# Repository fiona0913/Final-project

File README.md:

# Final-project
# Portable Soil Monitor

## Project Overview
The Portable Soil Monitor is a device designed for real-time monitoring of soil moisture. It uses a soil moisture sensor to collect data, analyzes trends with a machine learning algorithm, and predicts the next watering time to help users scientifically manage their plants.

---

## Features
- Real-time monitoring of soil moisture levels.
- Machine learning-based trend analysis to predict dryness for the next 1–2 days.
- Stepper motor-driven needle to display soil moisture status.
- LED indicators to provide watering reminders.
- Touch-sensitive button for manual data refresh.
- Solar-powered with backup lithium battery for continuous operation.

---

## Hardware Design

### 1. Overall Sketch

---

### 2. Sensing Device
- **Sensor**: DFRobot Capacitive Soil Moisture Sensor v2 (SEN0193).
- **Functionality**: Measures soil moisture levels and transmits data wirelessly to the main control chip (ESP32).
- **Power**: Solar panel as the primary power source, with a built-in lithium battery as backup.
- **Diagram**:

---

### 3. Display Device
- **Key Components**:
  - **Stepper Motor**: 28BYJ-48, drives a needle to show the soil moisture level.
  - **LEDs**: WS2812B RGB LEDs to indicate watering reminders.
  - **Touch Button**: TTP223 capacitive touch module for manual refresh.
- **Power**: Powered by a 3.7V lithium battery with optimized power consumption for stepper motors and LEDs.
- **Diagram**: *(Insert detailed sketch of the display device here.)*

---

## Communication and Workflow

### 1. Device Communication Flow

### 2. Functional Diagram

---

## Datasheets
The datasheets for all components used in this project can be found in the `datasheets/` folder. Key components include:
- **Soil Moisture Sensor**: SEN0193.
- **Wireless Communication Module**: ESP32-WROOM-32.
- **Stepper Motor**: 28BYJ-48 with ULN2003 driver.
- **RGB LEDs**: WS2812B.
- **Touch Button**: TTP223.
- **Power Management Module**: TP4056.

---

## How to Run the Project
1. Assemble all hardware components according to the design.
2. Upload the code to the ESP32 microcontroller.
3. Power on the device and let it begin monitoring soil moisture and displaying the results.

---

## Repository Structure

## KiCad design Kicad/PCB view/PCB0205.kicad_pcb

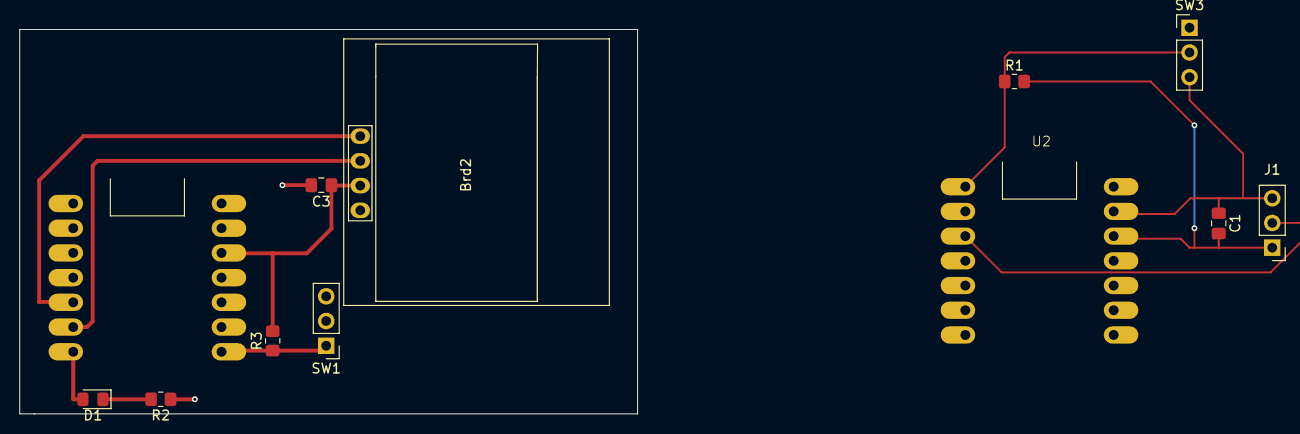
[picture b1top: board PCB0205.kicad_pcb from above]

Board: 2 copper layers, 63.5 x 39.5 mm, 12 parts (0 on the bottom side), 9 nets.

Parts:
Brd2: SSD1306; 128x64OLED
C1, C3: C; C_0805_2012Metric_Pad1.18x1.45mm_HandSolder
D1: LED; LED_0805_2012Metric_Pad1.15x1.40mm_HandSolder
J1: Soil Mositure Sen; PinHeader_1x03_P2.54mm_Vertical
R1, R2, R3: R; R_0805_2012Metric_Pad1.20x1.40mm_HandSolder
SW1: SW_Push; PinHeader_1x03_P2.54mm_Vertical
SW3: SW_SPDT; PinHeader_1x03_P2.54mm_Vertical
U1, U2: XIAO_ESP32_SENSE

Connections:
+3.3V: Brd2.2 (VCC), C1.2, C3.1, J1.1, R1.2, R3.2, U1.10 (3V3), U2.10 (3V3)
/signal: J1.2, U2.3 (GPIO3_A2_D2)
GND: Brd2.1 (GND), C1.1, C3.2, J1.3, R2.1, SW1.2, SW3.3 (C), U1.9 (GND), U2.9 (GND)
unnamed: Brd2.3 (SCL), U1.6 (GPIO6_A5_D5_SCL)
unnamed: Brd2.4 (SDA), U1.5 (GPIO4_A3_D3_SDA)
unnamed: D1.2 (A), U1.7 (GPIO43_TX_D6)
unnamed: D1.1 (K), R2.2
unnamed: R1.1, SW3.2 (B), U2.1 (GPIO1_A0_D0)
unnamed: R3.1, SW1.1, U1.14 (GPIO44_D7_RX)

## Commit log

2025-01-22 Add Soil monitor project files
2025-01-22 Update README with slide images
2025-01-22 Add .gitignore to exclude .DS_Store
2025-01-22 Add Sliders folder, CR2032 datasheet, and update README
2025-01-22 Fix Device Communication Flow image path
2025-01-22 Add Device Communication Flow image
2025-01-29 Add new KiCAD project for PCB design
2025-02-06 Updated Soil monitor project
2025-02-13 Saved local changes before pulling
2025-02-13 Removed embedded Git repository in battery
2025-02-13 Updated Soil monitor files, including battery
2025-02-13 Fixed battery folder issue
2025-02-26 Update Soil monitor project files
2025-03-10 Create sensor code
2025-03-10 Create Display code
2025-03-10 Rename sensor code to Sensor code
